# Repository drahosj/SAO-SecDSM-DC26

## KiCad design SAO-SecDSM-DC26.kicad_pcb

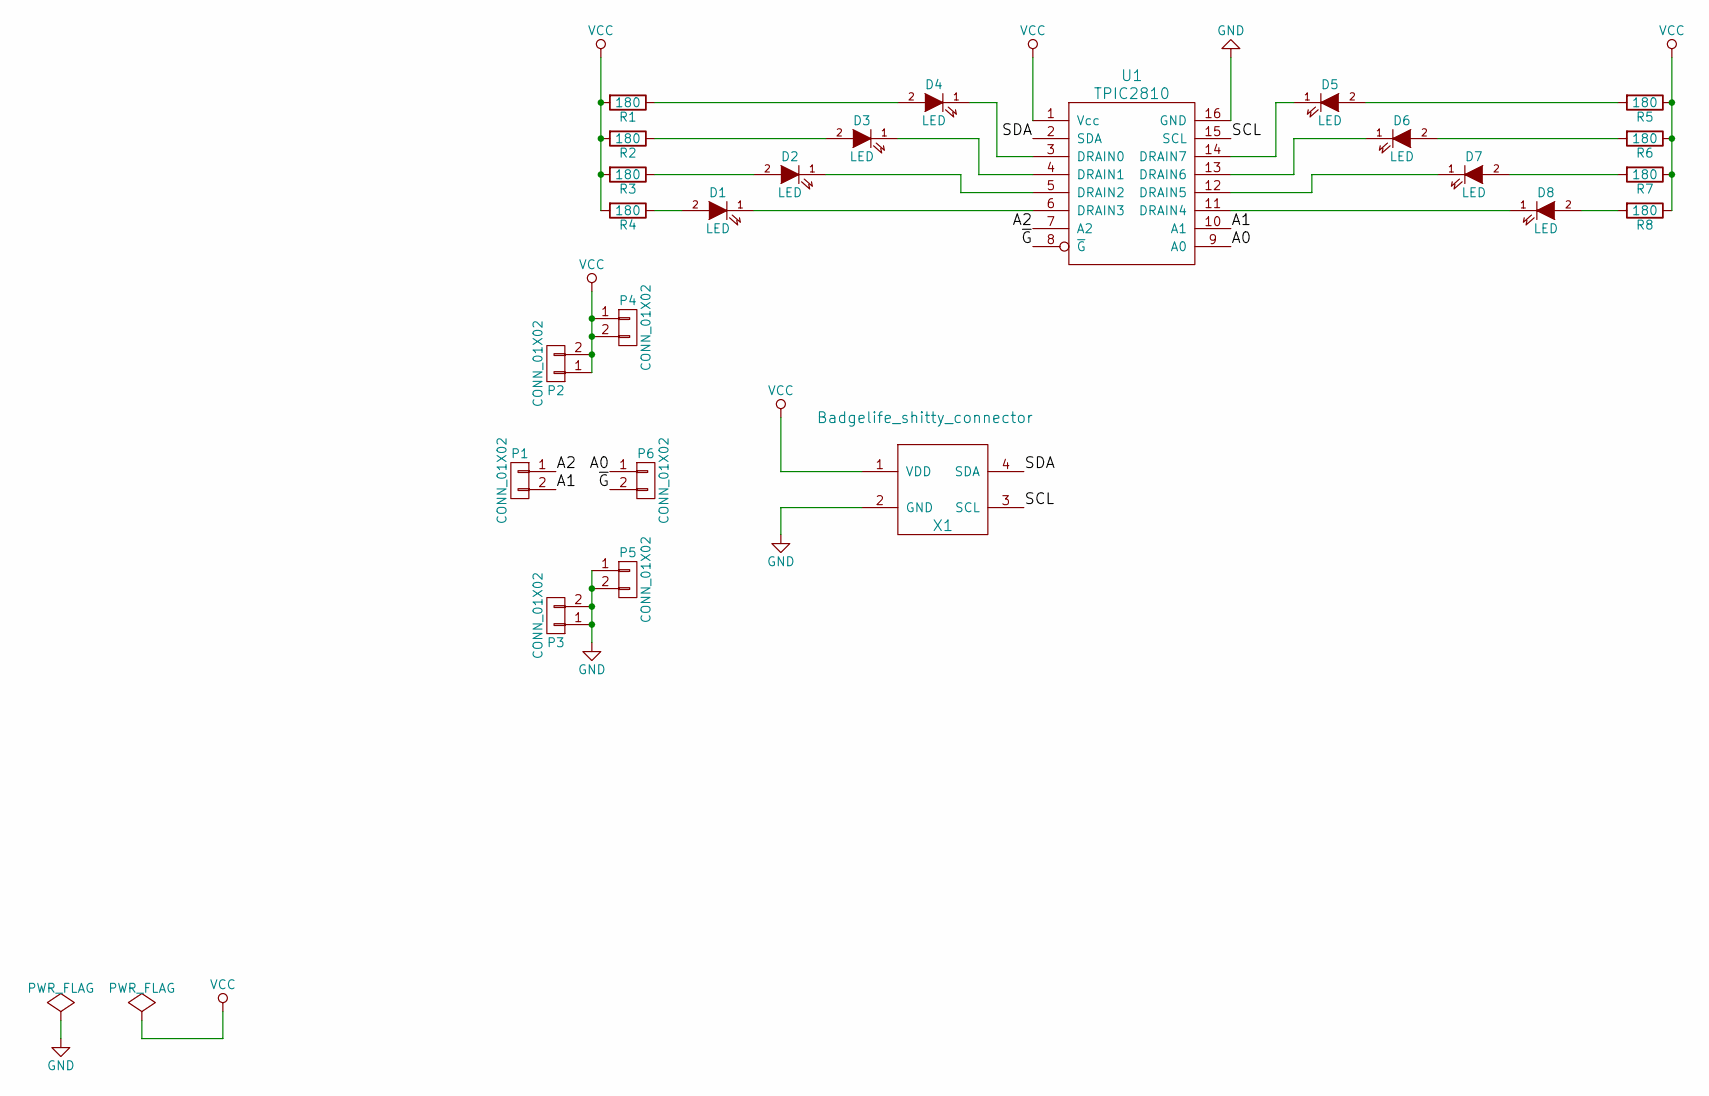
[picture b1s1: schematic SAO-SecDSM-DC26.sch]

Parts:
D1, D2, D3, D4, D5, D6, D7: LED; LED_0603_HandSoldering
D8: LED; LED_0805_HandSoldering
P1, P2, P3, P4, P5, P6: CONN_01X02; Pin_Header_Straight_1x02_Pitch2.54mm
R1, R2, R3, R4, R5, R6, R7, R8: 180; R_0603_HandSoldering
U1: TPIC2810; SOIC-16_3.9x9.9mm_Pitch1.27mm
X1: Badgelife_shitty_connector; Badgelife-Shitty-2x2

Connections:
/A0: P6.1, U1.9 (A0)
/A1: P1.2, U1.10 (A1)
/A2: P1.1, U1.7 (A2)
/SCL: U1.15 (SCL), X1.3 (SCL)
/SDA: U1.2 (SDA), X1.4 (SDA)
/~G: P6.2, U1.8 (~G)
GND: P3.1, P3.2, P5.1, P5.2, U1.16 (GND), X1.2 (GND)
unnamed: D1.1 (K), U1.6 (DRAIN3)
unnamed: D1.2 (A), R4.1
unnamed: D2.1 (K), U1.5 (DRAIN2)
unnamed: D2.2 (A), R3.1
unnamed: D3.1 (K), U1.4 (DRAIN1)
unnamed: D3.2 (A), R2.1
unnamed: D4.1 (K), U1.3 (DRAIN0)
unnamed: D4.2 (A), R1.1
unnamed: D5.1 (K), U1.14 (DRAIN7)
unnamed: D5.2 (A), R5.2
unnamed: D6.1 (K), U1.13 (DRAIN6)
unnamed: D6.2 (A), R6.2
unnamed: D7.1 (K), U1.12 (DRAIN5)
unnamed: D7.2 (A), R7.2
unnamed: D8.1 (K), U1.11 (DRAIN4)
unnamed: D8.2 (A), R8.2
VCC: P2.1, P2.2, P4.1, P4.2, R1.2, R2.2, R3.2, R4.2, R5.1, R6.1, R7.1, R8.1, U1.1 (Vcc), X1.1 (VDD)

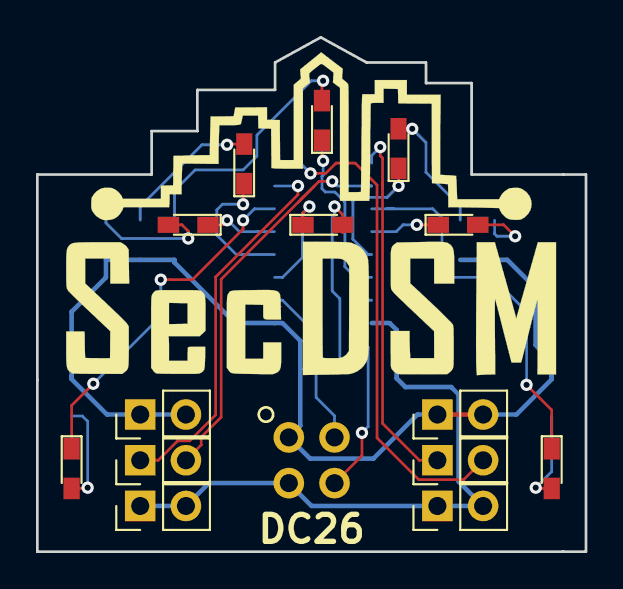
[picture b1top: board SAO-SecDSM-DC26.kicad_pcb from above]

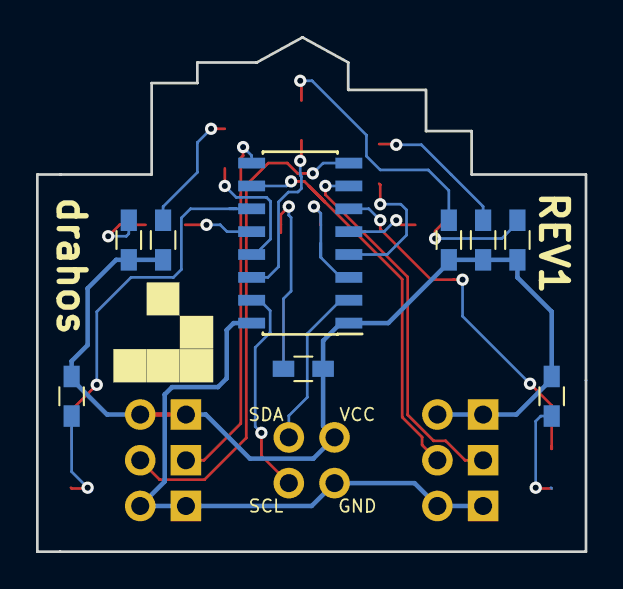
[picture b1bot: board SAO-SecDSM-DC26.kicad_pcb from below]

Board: 2 copper layers, 30.5 x 28.6 mm, 24 parts (9 on the bottom side), 24 nets.

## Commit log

2018-07-22 Rev1
2018-07-24 Added BoM
